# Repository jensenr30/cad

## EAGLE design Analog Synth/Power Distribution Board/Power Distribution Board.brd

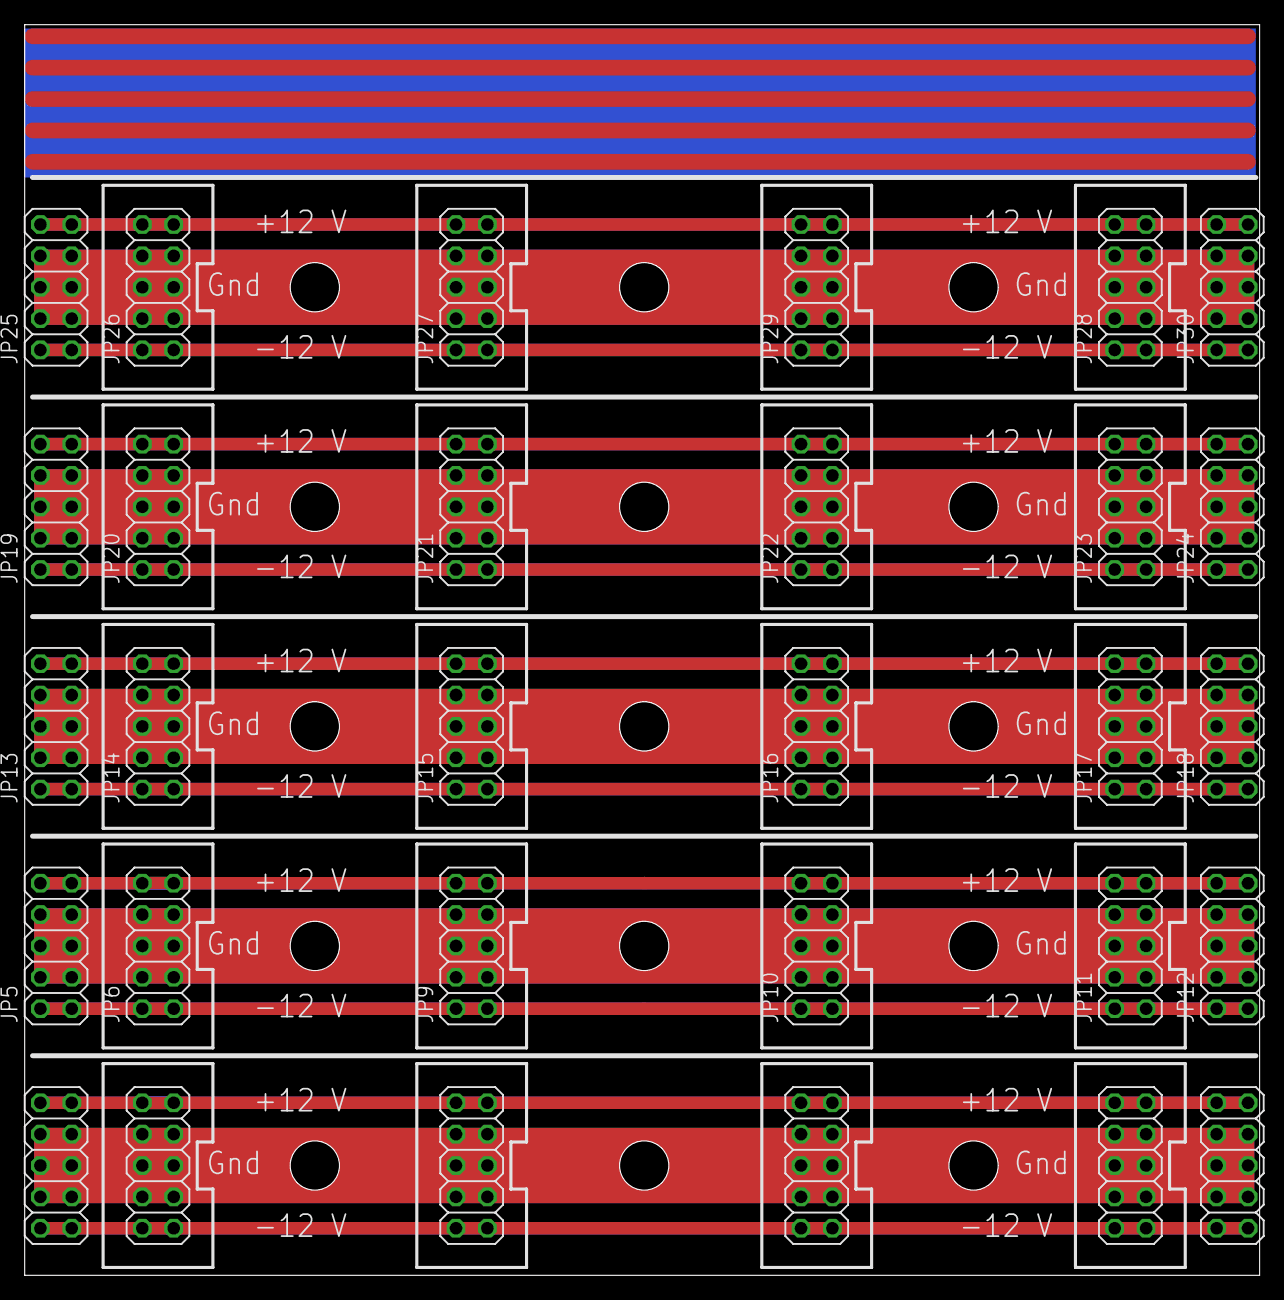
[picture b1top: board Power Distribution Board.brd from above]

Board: 2 copper layers, 100.0 x 101.3 mm, 30 parts (0 on the bottom side), 3 nets.

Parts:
JP1, JP2, JP3, JP4, JP5, JP6, JP7, JP8, JP9, JP10, JP11, JP12, JP13, JP14, JP15, JP16, JP17, JP18, JP19, JP20, JP21, JP22, JP23, JP24, JP25, JP26, JP27, JP28, JP29, JP30: 2X05

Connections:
+12V: JP1.1, JP1.2, JP2.1, JP2.2, JP3.1, JP3.2, JP4.1, JP4.2, JP5.1, JP5.2, JP6.1, JP6.2, JP7.1, JP7.2, JP8.1, JP8.2, JP9.1, JP9.2, JP10.1, JP10.2, JP11.1, JP11.2, JP12.1, JP12.2, JP13.1, JP13.2, JP14.1, JP14.2, JP15.1, JP15.2, JP16.1, JP16.2, JP17.1, JP17.2, JP18.1, JP18.2, JP19.1, JP19.2, JP20.1, JP20.2, JP21.1, JP21.2, JP22.1, JP22.2, JP23.1, JP23.2, JP24.1, JP24.2, JP25.1, JP25.2, JP26.1, JP26.2, JP27.1, JP27.2, JP28.1, JP28.2, JP29.1, JP29.2, JP30.1, JP30.2
-12V: JP1.9, JP1.10, JP2.9, JP2.10, JP3.9, JP3.10, JP4.9, JP4.10, JP5.9, JP5.10, JP6.9, JP6.10, JP7.9, JP7.10, JP8.9, JP8.10, JP9.9, JP9.10, JP10.9, JP10.10, JP11.9, JP11.10, JP12.9, JP12.10, JP13.9, JP13.10, JP14.9, JP14.10, JP15.9, JP15.10, JP16.9, JP16.10, JP17.9, JP17.10, JP18.9, JP18.10, JP19.9, JP19.10, JP20.9, JP20.10, JP21.9, JP21.10, JP22.9, JP22.10, JP23.9, JP23.10, JP24.9, JP24.10, JP25.9, JP25.10, JP26.9, JP26.10, JP27.9, JP27.10, JP28.9, JP28.10, JP29.9, JP29.10, JP30.9, JP30.10
GND: JP1.3, JP1.4, JP1.5, JP1.6, JP1.7, JP1.8, JP2.3, JP2.4, JP2.5, JP2.6, JP2.7, JP2.8, JP3.3, JP3.4, JP3.5, JP3.6, JP3.7, JP3.8, JP4.3, JP4.4, JP4.5, JP4.6, JP4.7, JP4.8, JP5.3, JP5.4, JP5.5, JP5.6, JP5.7, JP5.8, JP6.3, JP6.4, JP6.5, JP6.6, JP6.7, JP6.8, JP7.3, JP7.4, JP7.5, JP7.6, JP7.7, JP7.8, JP8.3, JP8.4, JP8.5, JP8.6, JP8.7, JP8.8, JP9.3, JP9.4, JP9.5, JP9.6, JP9.7, JP9.8, JP10.3, JP10.4, JP10.5, JP10.6, JP10.7, JP10.8, JP11.3, JP11.4, JP11.5, JP11.6, JP11.7, JP11.8, JP12.3, JP12.4, JP12.5, JP12.6, JP12.7, JP12.8, JP13.3, JP13.4, JP13.5, JP13.6, JP13.7, JP13.8, JP14.3, JP14.4, JP14.5, JP14.6, JP14.7, JP14.8, JP15.3, JP15.4, JP15.5, JP15.6, JP15.7, JP15.8, JP16.3, JP16.4, JP16.5, JP16.6, JP16.7, JP16.8, JP17.3, JP17.4, JP17.5, JP17.6, JP17.7, JP17.8, JP18.3, JP18.4, JP18.5, JP18.6, JP18.7, JP18.8, JP19.3, JP19.4, JP19.5, JP19.6, JP19.7, JP19.8, JP20.3, JP20.4, JP20.5, JP20.6, JP20.7, JP20.8, JP21.3, JP21.4, JP21.5, JP21.6, JP21.7, JP21.8, JP22.3, JP22.4, JP22.5, JP22.6, JP22.7, JP22.8, JP23.3, JP23.4, JP23.5, JP23.6, JP23.7, JP23.8, JP24.3, JP24.4, JP24.5, JP24.6, JP24.7, JP24.8, JP25.3, JP25.4, JP25.5, JP25.6, JP25.7, JP25.8, JP26.3, JP26.4, JP26.5, JP26.6, JP26.7, JP26.8, JP27.3, JP27.4, JP27.5, JP27.6, JP27.7, JP27.8, JP28.3, JP28.4, JP28.5, JP28.6, JP28.7, JP28.8, JP29.3, JP29.4, JP29.5, JP29.6, JP29.7, JP29.8, JP30.3, JP30.4, JP30.5, JP30.6, JP30.7, JP30.8

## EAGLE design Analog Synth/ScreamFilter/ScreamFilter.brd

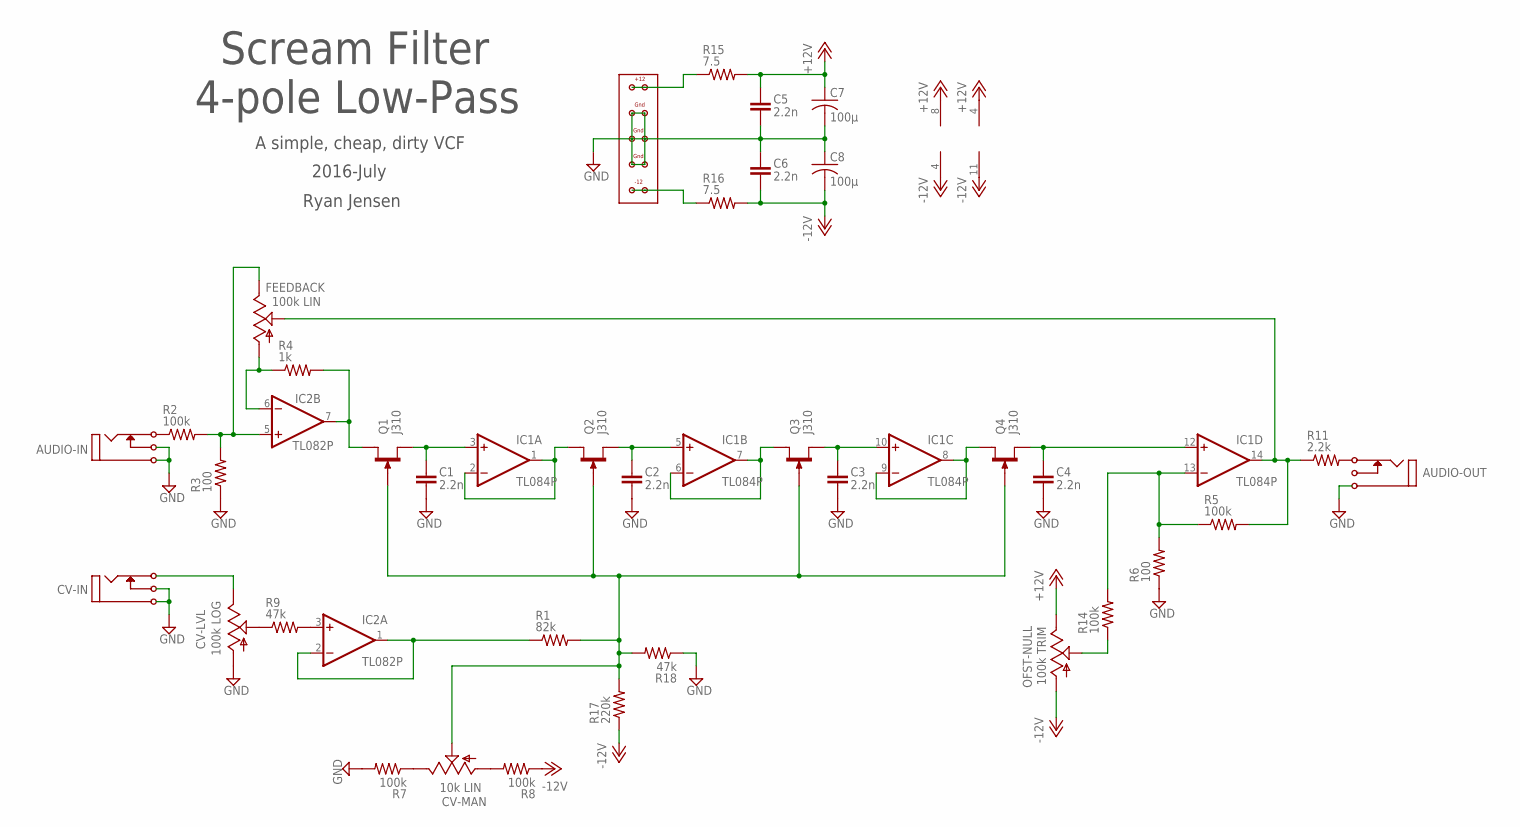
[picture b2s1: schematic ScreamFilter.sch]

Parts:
AUDIO-IN: I/O; MONO_JACK
AUDIO-OUT: I/O; MONO_JACK
C1, C2, C3, C4, C5, C6: 2.2n; C025-025X050
C7, C8: 100µ; C025-050X050
CV-IN: I/O; MONO_JACK
CV-LVL: 100k LOG; B64Y
CV-MAN: 10k LIN; B64Y
FEEDBACK: 100k LIN; B64Y
IC1: TL084P; DIL14
IC2: TL082P; DIL08
OFST-NULL: 100k TRIM; B64Y
Q1, Q2, Q3, Q4: J310; TO92R
R1: 82k; 0204/7
R2, R5, R7, R8, R14: 100k; 0204/7
R3, R6: 100; 0204/7
R4: 1k; 0204/7
R9, R18: 47k; 0204/7
R11: 2.2k; 0204/7
R15, R16: 7.5; 0204/7
R17: 220k; 0204/7
U$1: EURORACK-POWER

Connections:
+12V: C5.1, C7.1, IC1.4 (V+), IC2.8 (V+), OFST-NULL.E, R15.2
-12V: C6.2, C8.2, IC1.11 (V-), IC2.4 (V-), OFST-NULL.A, R8.1, R16.2, R17.1
GND: AUDIO-IN.P$1, AUDIO-IN.P$3 (P3), AUDIO-OUT.P$1, C1.2, C2.2, C3.2, C4.2, C5.2, C6.1, C7.2, C8.1, CV-IN.P$1, CV-IN.P$3 (P3), CV-LVL.A, R3.1, R6.1, R7.2, R18.1, U$1.P$3, U$1.P$4, U$1.P$5, U$1.P$6, U$1.P$7, U$1.P$8
unnamed: AUDIO-IN.P$2 (P2), R2.1
unnamed: FEEDBACK.E, IC2.5 (+IN), R2.2, R3.2
unnamed: IC2.7 (OUT), Q1.D, R4.2
unnamed: C1.1, IC1.3 (+IN), Q1.S
unnamed: IC1.1 (OUT), IC1.2 (-IN), Q2.D
unnamed: C2.1, IC1.5 (+IN), Q2.S
unnamed: IC1.6 (-IN), IC1.7 (OUT), Q3.D
unnamed: FEEDBACK.S, IC1.14 (OUT), R5.2, R11.1
unnamed: C3.1, IC1.10 (+IN), Q3.S
unnamed: IC1.8 (OUT), IC1.9 (-IN), Q4.D
unnamed: C4.1, IC1.12 (+IN), Q4.S
unnamed: CV-MAN.E, R7.1
unnamed: OFST-NULL.S, R14.1
unnamed: IC1.13 (-IN), R5.1, R6.2, R14.2
unnamed: CV-MAN.A, R8.2
unnamed: CV-IN.P$2 (P2), CV-LVL.E
unnamed: IC2.3 (+IN), R9.2
unnamed: CV-MAN.S, Q1.G, Q2.G, Q3.G, Q4.G, R1.2, R17.2, R18.2
unnamed: AUDIO-OUT.P$2 (P2), R11.2
unnamed: CV-LVL.S, R9.1
unnamed: FEEDBACK.A, IC2.6 (-IN), R4.1
unnamed: R16.1, U$1.P$9, U$1.P$10
unnamed: R15.1, U$1.P$1, U$1.P$2
unnamed: IC2.1 (OUT), IC2.2 (-IN), R1.1

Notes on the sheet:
Scream Filter 4-pole Low-Pass
A simple, cheap, dirty VCF
Ryan Jensen
2016-July

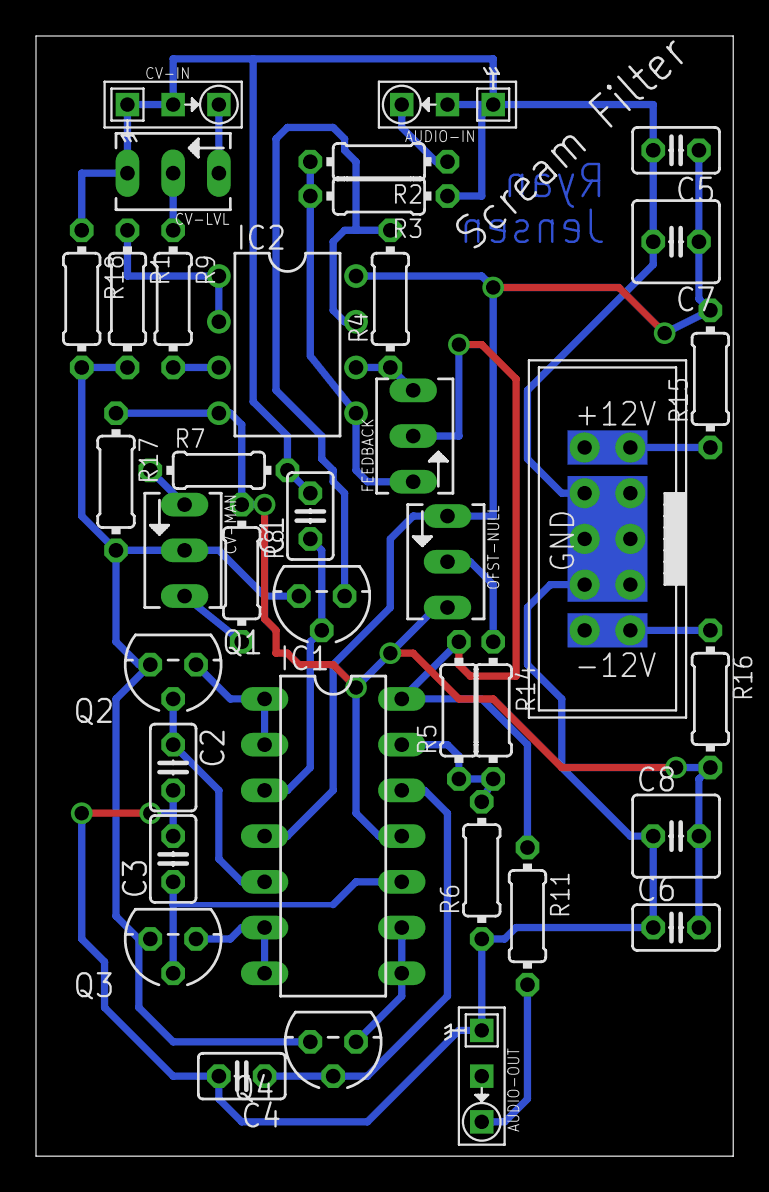
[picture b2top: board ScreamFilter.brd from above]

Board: 2 copper layers, 38.7 x 62.2 mm, 37 parts (0 on the bottom side), 27 nets.

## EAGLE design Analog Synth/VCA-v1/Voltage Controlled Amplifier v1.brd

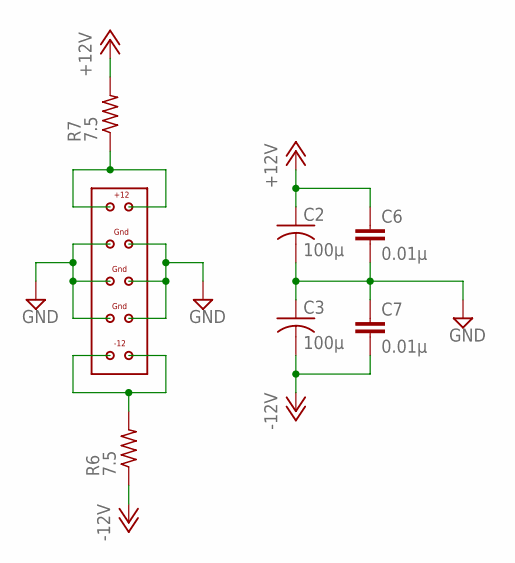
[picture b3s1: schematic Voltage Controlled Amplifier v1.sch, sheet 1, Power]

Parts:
C2, C3: 100µ; C025-050X050
C6, C7: 0.01µ; C2.5-2
R6, R7: 7.5; 0204/7
U$1: EURORACK-POWER

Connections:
+12V: C2.1, C6.1, R7.2; also elsewhere on the board
-12V: C3.2, C7.2, R6.1; also elsewhere on the board
GND: C2.2, C3.1, C6.2, C7.1, U$1.P$3, U$1.P$4, U$1.P$5, U$1.P$6, U$1.P$7, U$1.P$8; also elsewhere on the board
unnamed: R6.2, U$1.P$9, U$1.P$10
unnamed: R7.1, U$1.P$1, U$1.P$2

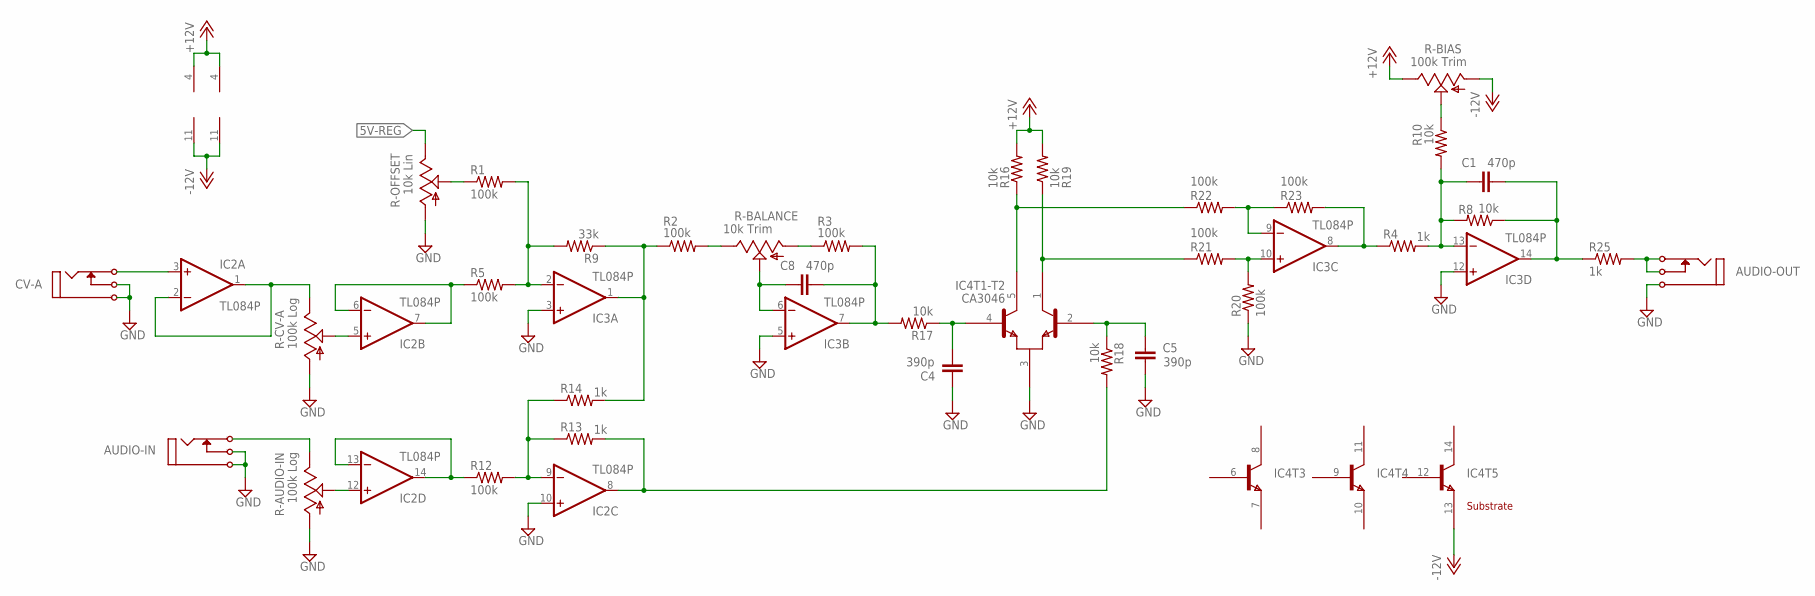
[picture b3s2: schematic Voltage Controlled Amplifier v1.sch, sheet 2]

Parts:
AUDIO-IN: I/O; MONO_JACK
AUDIO-OUT: I/O; MONO_JACK
C1, C8: 470p; C2.5-2
C4, C5: 390p; C2.5-2
CV-A: I/O; MONO_JACK
IC2, IC3: TL084P; DIL14
IC4: CA3046; DIL14
R1, R2, R3, R5, R12, R20, R21, R22, R23: 100k; 0204V
R4, R13, R14: 1k; 0204V
R8, R10, R16, R17, R19: 10k; 0204V
R9: 33k; 0204V
R18: 10k; 0204/7
R25: 1k; 0204/7
R-AUDIO-IN: 100k Log; B64Y
R-BALANCE: 10k Trim; B64Y
R-BIAS: 100k Trim; B64Y
R-CV-A: 100k Log; B64Y
R-OFFSET: 10k Lin; B64Y

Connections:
5V-REG: R-OFFSET.E
+12V: IC2.4 (V+), IC3.4 (V+), R16.2, R19.2, R-BIAS.E; also elsewhere on the board
-12V: IC2.11 (V-), IC3.11 (V-), IC4.13 (E), R-BIAS.A; also elsewhere on the board
GND: AUDIO-IN.P$1, AUDIO-IN.P$3 (P3), AUDIO-OUT.P$1, C4.1, C5.2, CV-A.P$1, CV-A.P$3 (P3), IC2.10 (+IN), IC3.3 (+IN), IC3.5 (+IN), IC3.12 (+IN), IC4.3 (E), R20.1, R-AUDIO-IN.A, R-CV-A.A, R-OFFSET.A; also elsewhere on the board
unnamed: IC2.6 (-IN), IC2.7 (OUT), R5.1
unnamed: C4.2, IC4.4 (B2), R17.1
unnamed: CV-A.P$2 (P2), IC2.3 (+IN)
unnamed: IC2.1 (OUT), IC2.2 (-IN), R-CV-A.E
unnamed: R2.2, R-BALANCE.E
unnamed: IC3.2 (-IN), R1.2, R5.2, R9.2
unnamed: R3.1, R-BALANCE.A
unnamed: AUDIO-IN.P$2 (P2), R-AUDIO-IN.E
unnamed: R10.1, R-BIAS.S
unnamed: R1.1, R-OFFSET.S
unnamed: IC2.5 (+IN), R-CV-A.S
unnamed: IC3.1 (OUT), R2.1, R9.1, R14.2
unnamed: IC2.13 (-IN), IC2.14 (OUT), R12.1
unnamed: IC2.12 (+IN), R-AUDIO-IN.S
unnamed: C1.1, IC3.13 (-IN), R4.2, R8.2, R10.2
unnamed: C5.1, IC4.2 (B1), R18.1
unnamed: IC2.9 (-IN), R12.2, R13.1, R14.1
unnamed: C8.2, IC3.7 (OUT), R3.2, R17.2
unnamed: IC4.5 (C2), R16.1, R22.1
unnamed: C8.1, IC3.6 (-IN), R-BALANCE.S
unnamed: IC4.1 (C1), R19.1, R21.1
unnamed: IC2.8 (OUT), R13.2, R18.2
unnamed: IC3.10 (+IN), R20.2, R21.2
unnamed: IC3.9 (-IN), R22.2, R23.1
unnamed: IC3.8 (OUT), R4.1, R23.2
unnamed: AUDIO-OUT.P$2 (P2), AUDIO-OUT.P$3 (P3), R25.2
unnamed: C1.2, IC3.14 (OUT), R8.1, R25.1

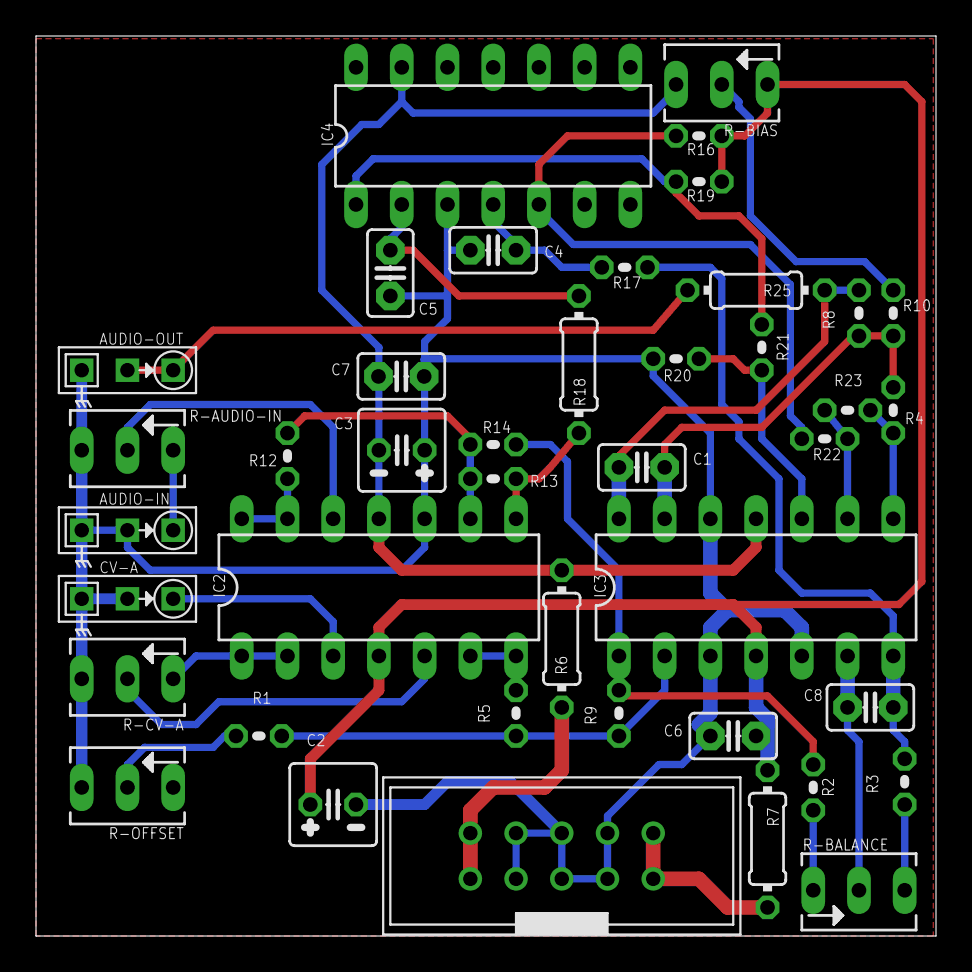
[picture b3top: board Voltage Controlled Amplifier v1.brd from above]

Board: 2 copper layers, 50.0 x 50.0 mm, 42 parts (0 on the bottom side), 32 nets.

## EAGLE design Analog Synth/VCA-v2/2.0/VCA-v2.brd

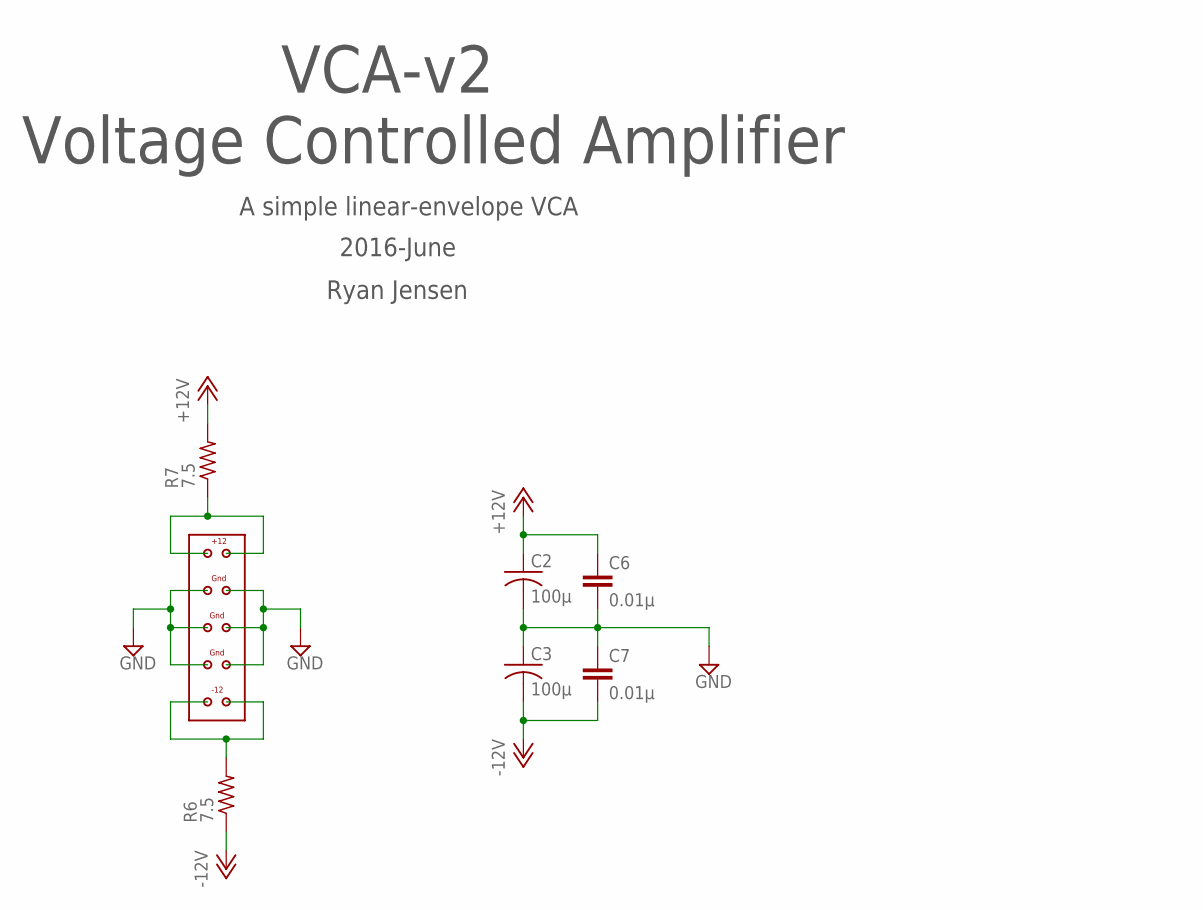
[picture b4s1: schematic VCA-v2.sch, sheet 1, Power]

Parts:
C2, C3: 100µ; C025-050X050
C6, C7: 0.01µ; C2.5-2
R6, R7: 7.5; R0603
U$1: EURORACK-POWER

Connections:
+12V: C2.1, C6.1, R7.2; also elsewhere on the board
-12V: C3.2, C7.2, R6.1; also elsewhere on the board
GND: C2.2, C3.1, C6.2, C7.1, U$1.P$3, U$1.P$4, U$1.P$5, U$1.P$6, U$1.P$7, U$1.P$8; also elsewhere on the board
unnamed: R6.2, U$1.P$9, U$1.P$10
unnamed: R7.1, U$1.P$1, U$1.P$2

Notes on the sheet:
VCA-v2 Voltage Controlled Amplifier
A simple linear-envelope VCA
Ryan Jensen
2016-June

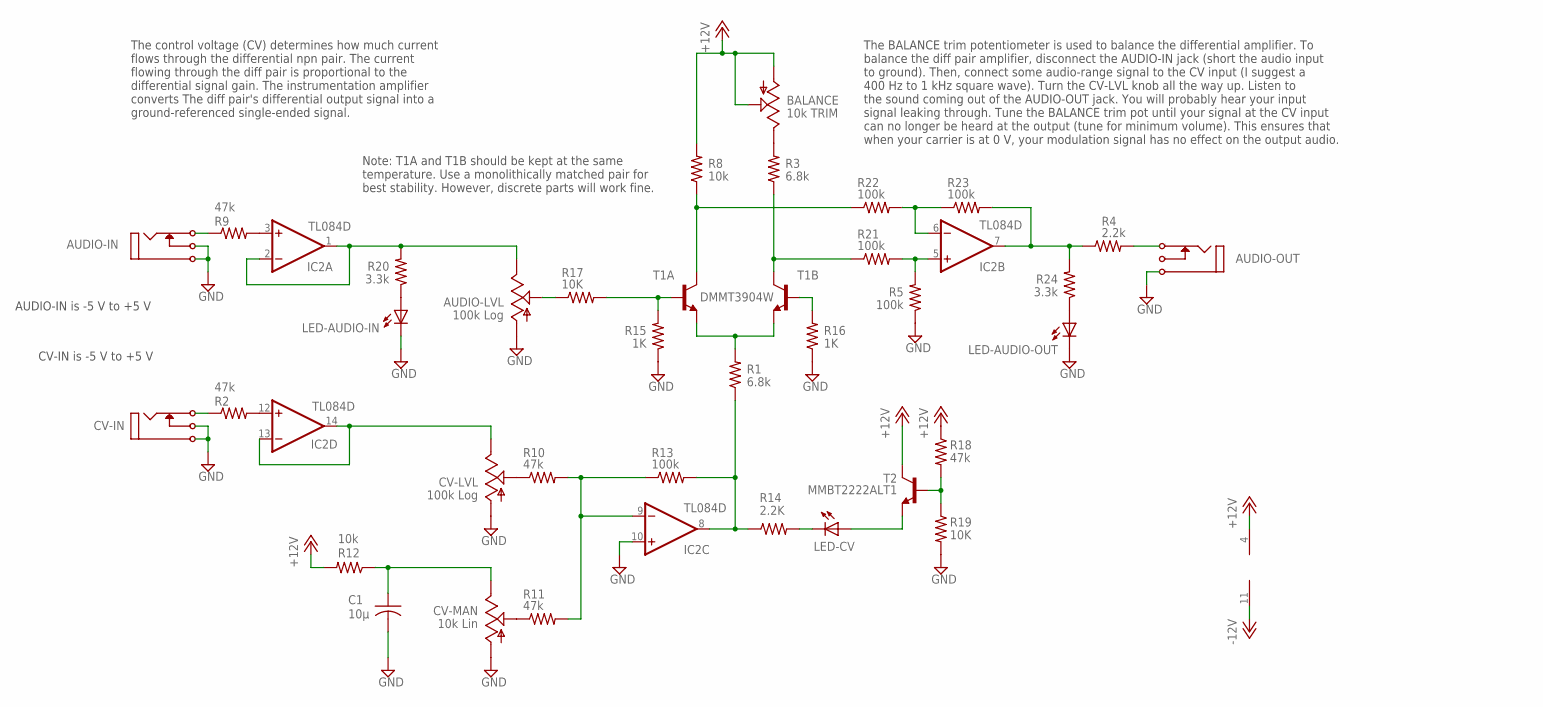
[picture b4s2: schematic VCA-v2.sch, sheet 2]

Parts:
AUDIO-IN: I/O; MONO_JACK
AUDIO-LVL: 100k Log; B64Y
AUDIO-OUT: I/O; MONO_JACK
BALANCE: 10k TRIM; B64Y
C1: 10µ; C025-050X050
CV-IN: I/O; MONO_JACK
CV-LVL: 100k Log; B64Y
CV-MAN: 10k Lin; B64Y
IC2: TL084D; SO14
LED-AUDIO-IN: TLLG4400; LED3MM
LED-AUDIO-OUT: TLLG4400; LED3MM
LED-CV: TLLG4400; LED3MM
R1, R3: 6.8k; R0603
R2, R9, R10, R11, R18: 47k; R0603
R4: 2.2k; R0603
R5, R13, R21, R22, R23: 100k; R0603
R8, R12: 10k; R0603
R14: 2.2K; R0603
R15, R16: 1K; R0603
R17, R19: 10K; R0603
R20, R24: 3.3k; R0603
T1: DMMT3904W; SOT363
T2: MMBT2222ALT1; SOT23-BEC

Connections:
+12V: BALANCE.A, BALANCE.S, IC2.4 (V+), R8.2, R12.2, R18.1, T2.C; also elsewhere on the board
-12V: IC2.11 (V-); also elsewhere on the board
GND: AUDIO-IN.P$1, AUDIO-IN.P$3 (P3), AUDIO-LVL.A, AUDIO-OUT.P$1, C1.2, CV-IN.P$1, CV-IN.P$3 (P3), CV-LVL.A, CV-MAN.A, IC2.10 (+IN), LED-AUDIO-IN.K (C), LED-AUDIO-OUT.K (C), R5.1, R15.1, R16.1, R19.2; also elsewhere on the board
LED_SUPPLY: LED-CV.A, T2.E
unnamed: IC2.8 (OUT), R1.1, R13.2, R14.1
unnamed: BALANCE.E, R3.2
unnamed: IC2.12 (+IN), R2.2
unnamed: CV-LVL.E, IC2.13 (-IN), IC2.14 (OUT)
unnamed: CV-IN.P$2 (P2), R2.1
unnamed: AUDIO-IN.P$2 (P2), R9.1
unnamed: IC2.3 (+IN), R9.2
unnamed: AUDIO-LVL.E, IC2.1 (OUT), IC2.2 (-IN), R20.2
unnamed: CV-LVL.S, R10.1
unnamed: LED-CV.K (C), R14.2
unnamed: CV-MAN.S, R11.1
unnamed: C1.1, CV-MAN.E, R12.1
unnamed: R1.2, T1.4 (E), T1.5 (E)
unnamed: R15.2, R17.2, T1.1 (B)
unnamed: IC2.9 (-IN), R10.2, R11.2, R13.1
unnamed: AUDIO-LVL.S, R17.1
unnamed: R16.2, T1.2 (B)
unnamed: R18.2, R19.1, T2.B
unnamed: LED-AUDIO-IN.A, R20.1
unnamed: LED-AUDIO-OUT.A, R24.1
unnamed: R8.1, R22.1, T1.6 (C)
unnamed: R3.1, R21.1, T1.3 (C)
unnamed: IC2.5 (+IN), R5.2, R21.2
unnamed: IC2.6 (-IN), R22.2, R23.1
unnamed: IC2.7 (OUT), R4.1, R23.2, R24.2
unnamed: AUDIO-OUT.P$2 (P2), R4.2

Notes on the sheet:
The control voltage (CV) determines how much current flows through the differential npn pair. The current flowing through the diff pair is proportional to the differential signal gain. The instrumentation amplifier converts The diff pair's differential output signal into a ground-referenced single-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
The BALANCE trim potentiometer is used to balance the differential amplifier. To balance the diff pair amplifier, disconnect the AUDIO-IN jack (short the audio input to ground). Then, connect some audio-range signal to the CV input (I suggest a 400 Hz to 1 kHz square wave). Turn the CV-LVL knob all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
Note: T1A and T1B should be kept at the same temperature. Use a monolithically matched pair for best stability. However, discrete parts will work fine.
AUDIO-IN is -5 V to +5 V
CV-IN is -5 V to +5 V

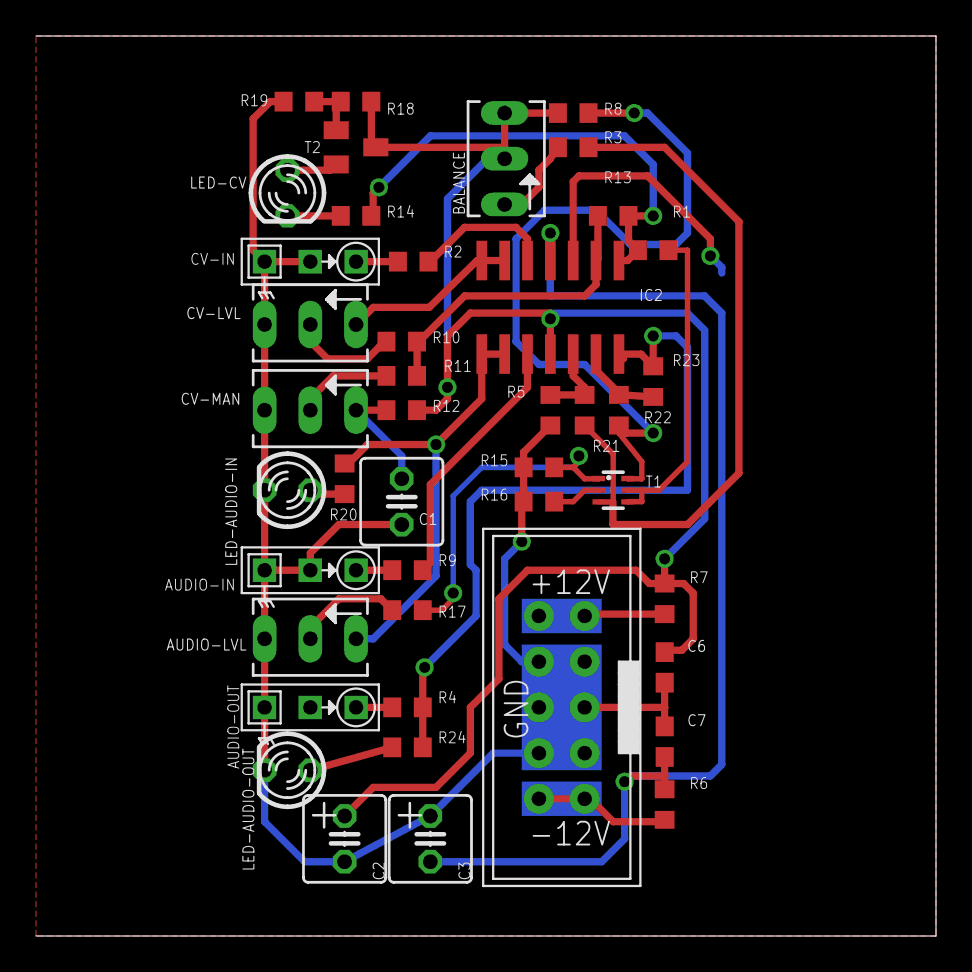
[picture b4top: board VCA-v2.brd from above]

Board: 2 copper layers, 50.0 x 50.0 mm, 43 parts (0 on the bottom side), 32 nets.

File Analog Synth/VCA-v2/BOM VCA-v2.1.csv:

"Qty","Value","Device","Package","Parts","Description"
"2","0.01µ","C-EUC0603","C0603","C6, C7","CAPACITOR, European symbol"
"5","100k","R-US_R0603","R0603","R5, R13, R21, R22, R23","RESISTOR, American symbol"
"2","100k Log","TRIM_US-B64Y","B64Y","AUDIO-LVL, CV-LVL","POTENTIOMETER"
"2","100µ","C-US025-050X050","C025-050X050","C2, C3","CAPACITOR, American symbol"
"2","10K","R-US_R0603","R0603","R17, R19","RESISTOR, American symbol"
"2","10k","R-US_R0603","R0603","R8, R12","RESISTOR, American symbol"
"1","10k Lin","TRIM_US-B64Y","B64Y","CV-MAN","POTENTIOMETER"
"1","10k TRIM","TRIM_US-B64Y","B64Y","BALANCE","POTENTIOMETER"
"1","10µ","C-US025-050X050","C025-050X050","C1","CAPACITOR, American symbol"
"2","1K","R-US_R0603","R0603","R15, R16","RESISTOR, American symbol"
"1","2.2K","R-US_R0603","R0603","R14","RESISTOR, American symbol"
"1","2.2k","R-US_R0603","R0603","R4","RESISTOR, American symbol"
"2","3.3k","R-US_R0603","R0603","R20, R24","RESISTOR, American symbol"
"5","47k","R-US_R0603","R0603","R2, R9, R10, R11, R18","RESISTOR, American symbol"
"2","6.8k","R-US_R0603","R0603","R1, R3","RESISTOR, American symbol"
"2","7.5","R-US_R0603","R0603","R6, R7","RESISTOR, American symbol"
"1","DMMT3904W","DMMT3904W","SOT363","T1",""
"1","EURORACK-POWER","EURORACK-POWER","EURORACK-POWER","U$1",""
"3","I/O","MONO_JACK","MONO_JACK","AUDIO-IN, AUDIO-OUT, CV-IN",""
"1","MMBT2222ALT1","MMBT2222ALT1-NPN-SOT23-BEC","SOT23-BEC","T2","NPN Transistror"
"1","TL084D","TL084D","SO14","IC2","OP AMP"
"3","TLLG4400","TLLG4400","LED3MM","LED-AUDIO-IN, LED-AUDIO-OUT, LED-CV","Low Current (2mA) LED 3 mm Tinted Diffused Package color GREEN"
